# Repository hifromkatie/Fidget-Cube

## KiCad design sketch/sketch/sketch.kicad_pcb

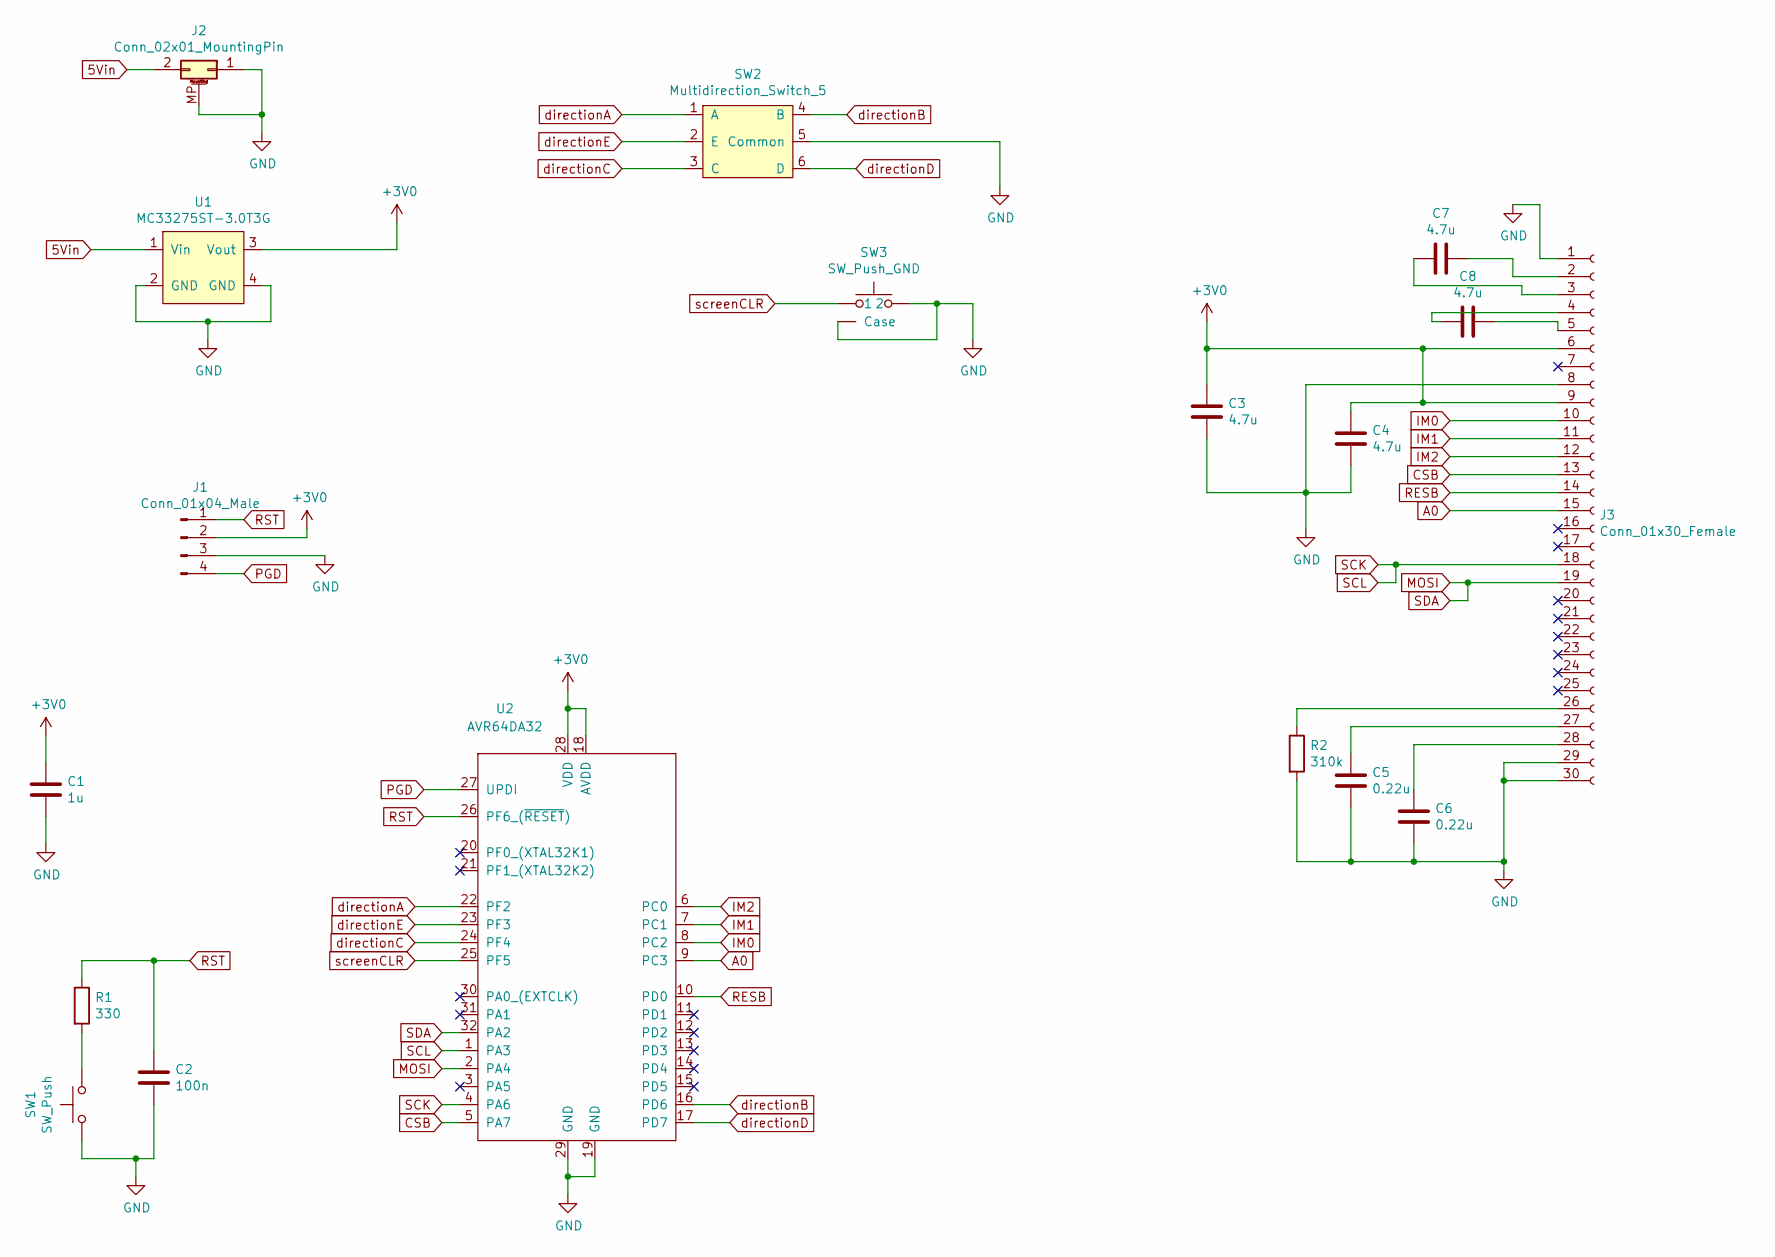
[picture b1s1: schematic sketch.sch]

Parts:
C1: 1u; C_0603_1608Metric_Pad1.08x0.95mm_HandSolder; Farnell Part Number 2409038
C2: 100n; C_0603_1608Metric_Pad1.08x0.95mm_HandSolder; Farnell Part Number 2320813
C3, C4, C7, C8: 4.7u; C_0603_1608Metric_Pad1.08x0.95mm_HandSolder; Farnell Part Number 9227784
C5, C6: 0.22u; C_0603_1608Metric_Pad1.08x0.95mm_HandSolder; Farnell Part Number 2627437
J1: Conn_01x04_Male; PinHeader_1x04_P2.54mm_Vertical
J2: Conn_02x01_MountingPin; Molex_PicoBlade_53398-0271_1x02-1MP_P1.25mm_Vertical; Farnell Part Number 1125366
J3: Conn_01x30_Female; screenConnector_30pin_0.7pitch
R1: 330; R_0603_1608Metric_Pad0.98x0.95mm_HandSolder; Farnell Part Number 2447339
R2: 310k; R_0603_1608Metric_Pad0.98x0.95mm_HandSolder; Farnell Part Number 2337128
SW1: SW_Push; WS-TASV; Farnell Part Number 1867991
SW2: Multidirection_Switch_5; MCMT5; Farnell Part Number 1316987
SW3: SW_Push_GND; MSLPT5252-BG; Farnell Part Number 2991002
U1: MC33275ST-3.0T3G; SOT-223; Farnell Part Number 2728244
U2: AVR64DA32; TQFP-32_7x7mm_P0.8mm; Farnell Part Number 3576891

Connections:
5Vin: J2.2, U1.1 (Vin)
+3V0: C1.1, C3.1, C4.1, J1.2, J3.6, J3.9, U1.3 (Vout), U2.18 (AVDD), U2.28 (VDD)
A0: J3.15, U2.9 (PC3)
CSB: J3.13, U2.5 (PA7)
GND: C1.2, C2.2, C3.2, C4.2, C5.2, C6.2, J1.3, J2.1, J2.MP (MountPin), J3.1, J3.8, J3.29, J3.30, R2.2, SW1.1, SW2.5 (Common), SW3.2, SW3.3 (Case), U1.2 (GND), U1.4 (GND), U2.19 (GND), U2.29 (GND)
IM0: J3.10, U2.8 (PC2)
IM1: J3.11, U2.7 (PC1)
IM2: J3.12, U2.6 (PC0)
MOSI: J3.19, U2.2 (PA4), U2.32 (PA2)
unnamed: C5.1, J3.27
unnamed: C6.1, J3.28
unnamed: C7.1, J3.2
unnamed: C7.2, J3.3
unnamed: C8.1, J3.5
unnamed: C8.2, J3.4
unnamed: J3.26, R2.1
unnamed: R1.2, SW1.2
PGD: J1.4, U2.27 (UPDI)
RESB: J3.14, U2.10 (PD0)
RST: C2.1, J1.1, R1.1, U2.26 (PF6_(~RESET~))
SCK: J3.18, U2.1 (PA3), U2.4 (PA6)
directionA: SW2.1 (A), U2.22 (PF2)
directionB: SW2.4 (B), U2.16 (PD6)
directionC: SW2.3 (C), U2.24 (PF4)
directionD: SW2.6 (D), U2.17 (PD7)
directionE: SW2.2 (E), U2.23 (PF3)
screenCLR: SW3.1, U2.25 (PF5)

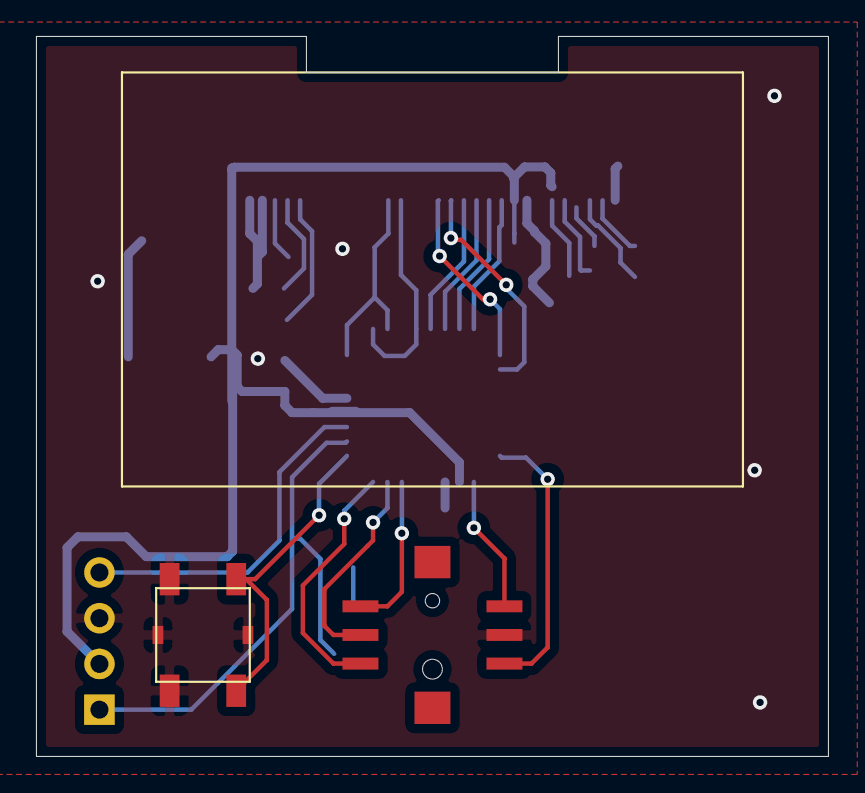
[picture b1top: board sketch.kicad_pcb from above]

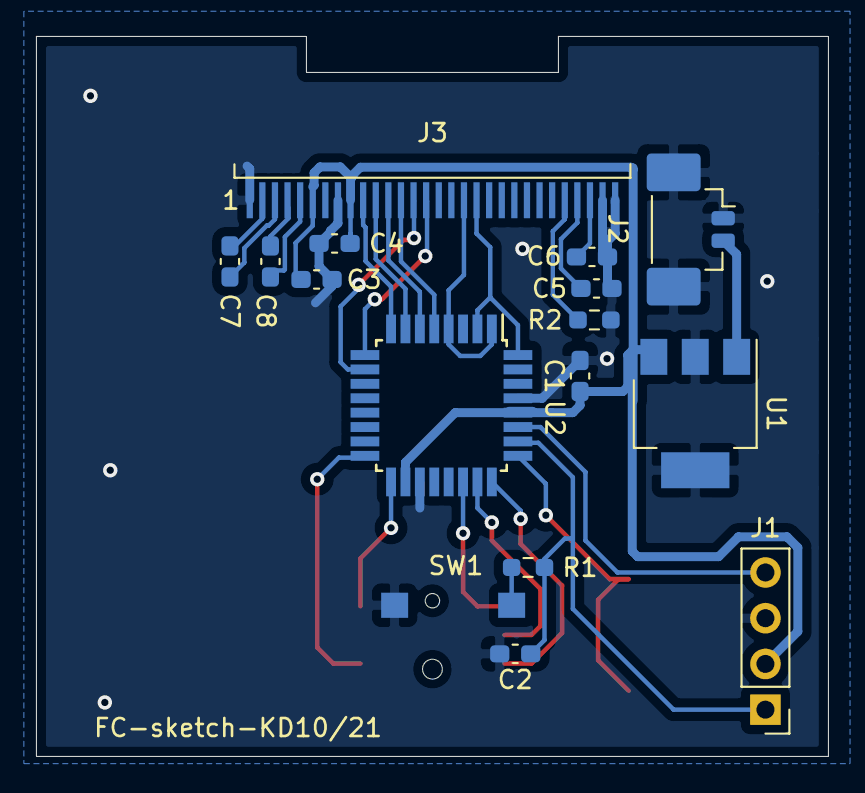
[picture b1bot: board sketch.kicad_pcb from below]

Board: 2 copper layers, 44.0 x 40.0 mm, 18 parts (16 on the bottom side), 27 nets.

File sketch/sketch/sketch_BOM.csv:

Source:,/home/katie/Projects/FidgetCube/circuit/sketch/sketch/sketch.sch,,,,,,
Date:,Tue 23 Nov 2021 22:22:43 GMT,,,,,,
Tool:,Eeschema 5.1.10-88a1d61d58~90~ubuntu20.04.1,,,,,,
Generator:,/usr/share/kicad/plugins/bom_csv_grouped_by_value.py,,,,,,
Component Count:,18,,,,,,
,,,,,,,
Individual Components:,,,,,,,
,,,,,,,
Item,Qty,Reference(s),Value,LibPart,Footprint,Datasheet,Farnell Part Number
,,C1,1u,Device:C,Capacitor_SMD:C_0603_1608Metric_Pad1.08x0.95mm_HandSolder,~,2409038
,,C2,100n,Device:C,Capacitor_SMD:C_0603_1608Metric_Pad1.08x0.95mm_HandSolder,~,2320813
,,C3,4.7u,Device:C,Capacitor_SMD:C_0603_1608Metric_Pad1.08x0.95mm_HandSolder,~,9227784
,,C4,4.7u,Device:C,Capacitor_SMD:C_0603_1608Metric_Pad1.08x0.95mm_HandSolder,~,9227784
,,C5,0.22u,Device:C,Capacitor_SMD:C_0603_1608Metric_Pad1.08x0.95mm_HandSolder,~,2627437
,,C6,0.22u,Device:C,Capacitor_SMD:C_0603_1608Metric_Pad1.08x0.95mm_HandSolder,~,2627437
,,C7,4.7u,Device:C,Capacitor_SMD:C_0603_1608Metric_Pad1.08x0.95mm_HandSolder,~,9227784
,,C8,4.7u,Device:C,Capacitor_SMD:C_0603_1608Metric_Pad1.08x0.95mm_HandSolder,~,9227784
,,J1,Conn_01x04_Male,Connector:Conn_01x04_Male,Connector_PinHeader_2.54mm:PinHeader_1x04_P2.54mm_Vertical,~,-
,,J2,Conn_02x01_MountingPin,Connector_Generic_MountingPin:Conn_02x01_MountingPin,Connector_Molex:Molex_PicoBlade_53398-0271_1x02-1MP_P1.25mm_Vertical,~,1125366
,,J3,Conn_01x30_Female,Connector:Conn_01x30_Female,My_Footprints:screenConnector_30pin_0.7pitch,~,-
,,R1,330,Device:R,Resistor_SMD:R_0603_1608Metric_Pad0.98x0.95mm_HandSolder,~,2447339
,,R2,310k,Device:R,Resistor_SMD:R_0603_1608Metric_Pad0.98x0.95mm_HandSolder,~,2337128
,,SW1,SW_Push,Switch:SW_Push,My_Footprints:WS-TASV,https://www.farnell.com/datasheets/1913847.pdf,1867991
,,SW2,Multidirection_Switch_5,My_Library:Multidirection_Switch_5,My_Footprints:MCMT5,https://www.farnell.com/datasheets/3169924.pdf,1316987
,,SW3,SW_Push_GND,My_Library:SW_Push_GND,My_Footprints:MSLPT5252-BG,https://uk.farnell.com/alcoswitch-te-connectivity/mslpt5252b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,2991002
,,U1,MC33275ST-3.0T3G,My_Library:MC33275ST-3.0T3G,Package_TO_SOT_SMD:SOT-223,https://www.farnell.com/datasheets/1904484.pdf,2728244
,,U2,AVR64DA32,My_Library:AVR64DA32,Package_QFP:TQFP-32_7x7mm_P0.8mm,https://www.farnell.com/datasheets/3165060.pdf,3576891
,,,,,,,
,,,,,,,
,,,,,,,
Collated Components:,,,,,,,
,,,,,,,
Item,Qty,Reference(s),Value,LibPart,Footprint,Datasheet,F
1,1,C1,1u,Device:C,Capacitor_SMD:C_0603_1608Metric_Pad1.08x0.95mm_HandSolder,~,2409038
2,1,C2,100n,Device:C,Capacitor_SMD:C_0603_1608Metric_Pad1.08x0.95mm_HandSolder,~,2320813
3,4,"C3, C4, C7, C8",4.7u,Device:C,Capacitor_SMD:C_0603_1608Metric_Pad1.08x0.95mm_HandSolder,~,9227784
4,2,"C5, C6",0.22u,Device:C,Capacitor_SMD:C_0603_1608Metric_Pad1.08x0.95mm_HandSolder,~,2627437
5,1,J1,Conn_01x04_Male,Connector:Conn_01x04_Male,Connector_PinHeader_2.54mm:PinHeader_1x04_P2.54mm_Vertical,~,-
6,1,J2,Conn_02x01_MountingPin,Connector_Generic_MountingPin:Conn_02x01_MountingPin,Connector_Molex:Molex_PicoBlade_53398-0271_1x02-1MP_P1.25mm_Vertical,~,1125366
7,1,J3,Conn_01x30_Female,Connector:Conn_01x30_Female,My_Footprints:screenConnector_30pin_0.7pitch,~,-
8,1,R1,330,Device:R,Resistor_SMD:R_0603_1608Metric_Pad0.98x0.95mm_HandSolder,~,2447339
9,1,R2,310k,Device:R,Resistor_SMD:R_0603_1608Metric_Pad0.98x0.95mm_HandSolder,~,2337128
10,1,SW1,SW_Push,Switch:SW_Push,My_Footprints:WS-TASV,https://www.farnell.com/datasheets/1913847.pdf,1867991
11,1,SW2,Multidirection_Switch_5,My_Library:Multidirection_Switch_5,My_Footprints:MCMT5,https://www.farnell.com/datasheets/3169924.pdf,1316987
12,1,SW3,SW_Push_GND,My_Library:SW_Push_GND,My_Footprints:MSLPT5252-BG,https://uk.farnell.com/alcoswitch-te-connectivity/mslpt5252b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,2991002
13,1,U1,MC33275ST-3.0T3G,My_Library:MC33275ST-3.0T3G,Package_TO_SOT_SMD:SOT-223,https://www.farnell.com/datasheets/1904484.pdf,2728244
14,1,U2,AVR64DA32,My_Library:AVR64DA32,Package_QFP:TQFP-32_7x7mm_P0.8mm,https://www.farnell.com/datasheets/3165060.pdf,3576891

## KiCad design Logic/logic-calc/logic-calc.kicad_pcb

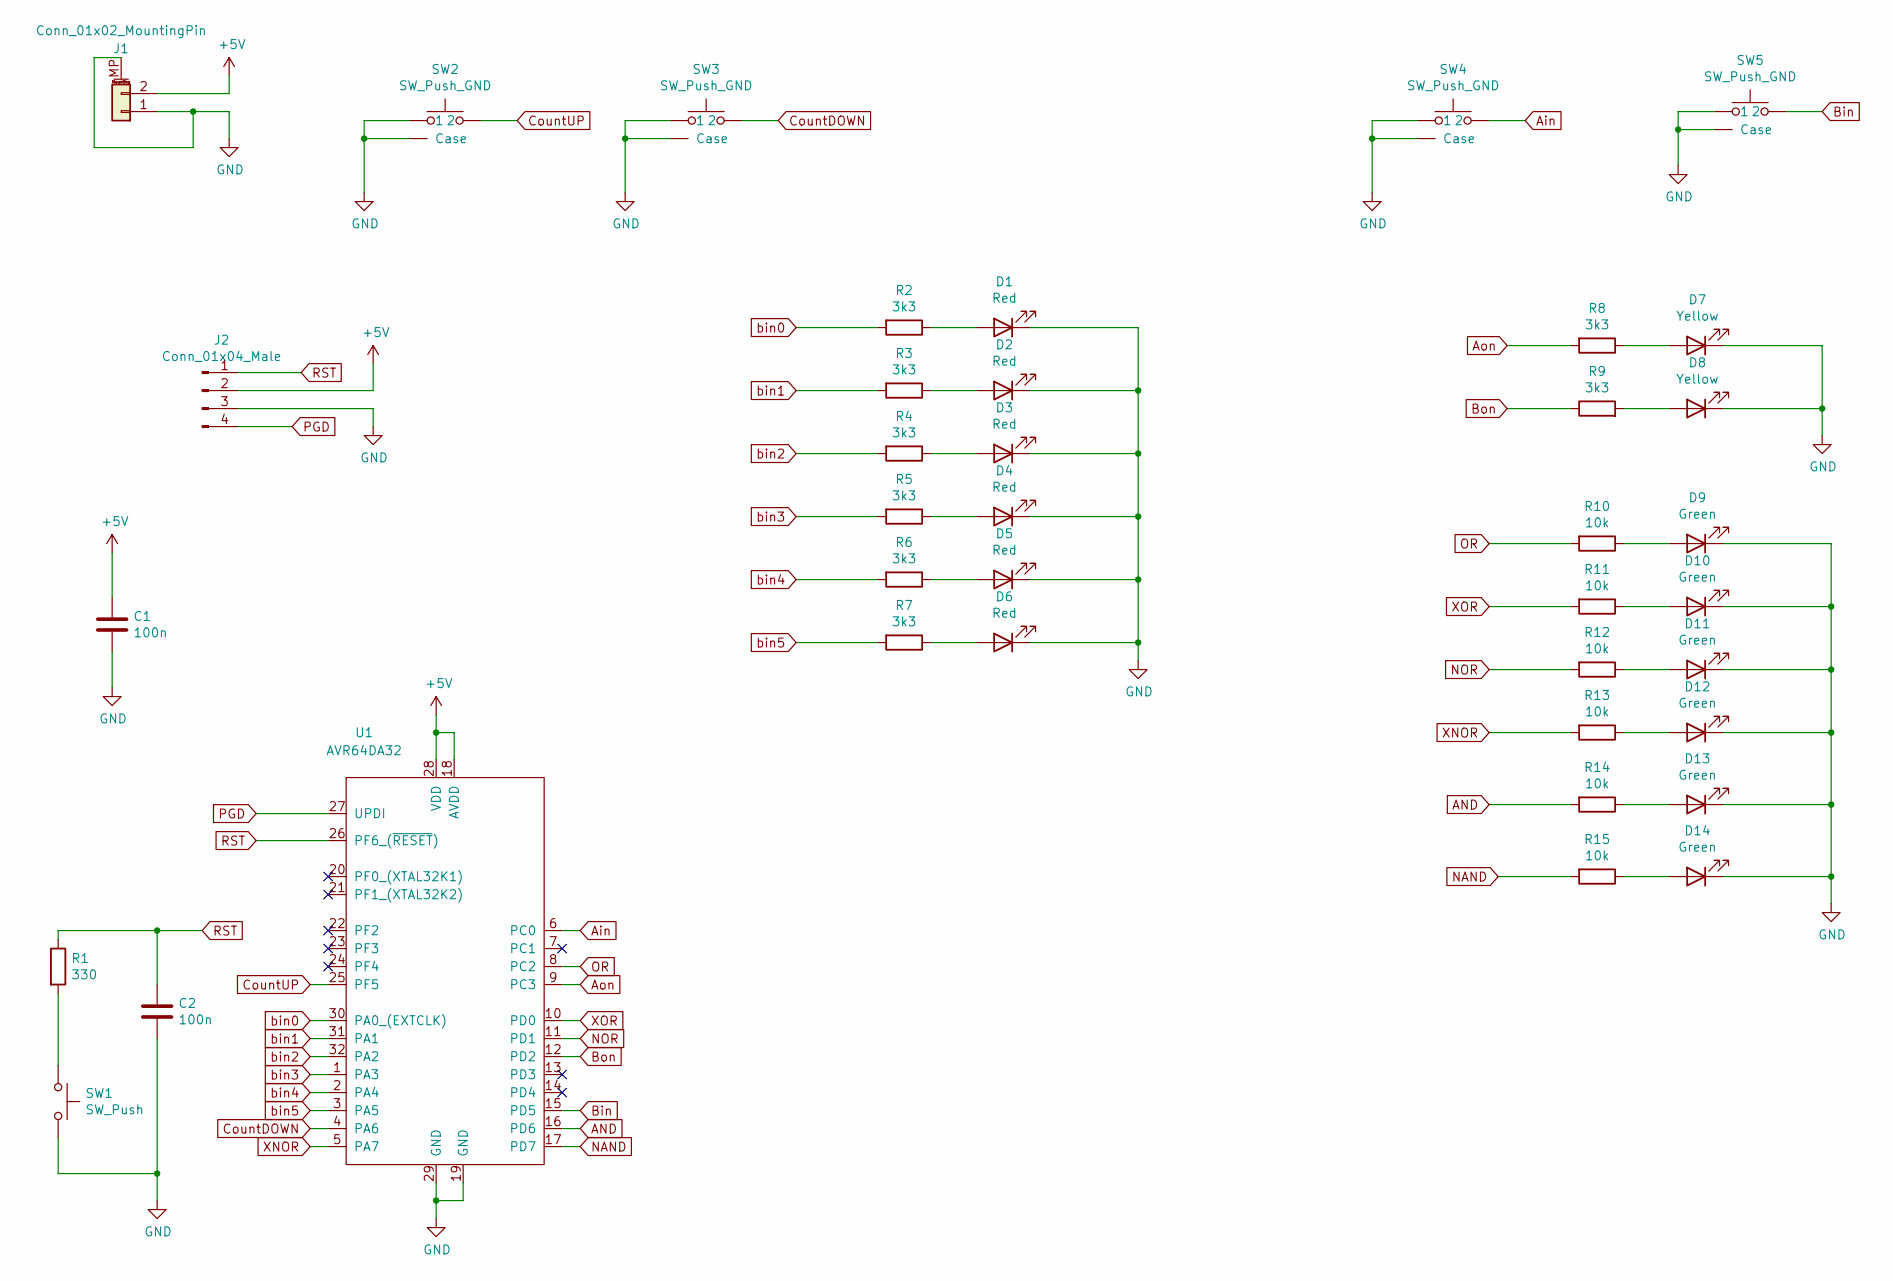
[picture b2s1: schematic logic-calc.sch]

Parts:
C1, C2: 100n; C_0603_1608Metric_Pad1.08x0.95mm_HandSolder
D1, D2, D3, D4, D5, D6: Red; LED_0805_2012Metric_Pad1.15x1.40mm_HandSolder
D7, D8: Yellow; LED_0805_2012Metric_Pad1.15x1.40mm_HandSolder
D9, D10, D11, D12, D13, D14: Green; LED_0805_2012Metric_Pad1.15x1.40mm_HandSolder
J1: Conn_01x02_MountingPin; Molex_PicoBlade_53398-0271_1x02-1MP_P1.25mm_Vertical
J2: Conn_01x04_Male; PinHeader_1x04_P2.54mm_Vertical
R1: 330; R_0603_1608Metric_Pad0.98x0.95mm_HandSolder
R2, R3, R4, R5, R6, R7, R8, R9: 3k3; R_0603_1608Metric_Pad0.98x0.95mm_HandSolder
R10, R11, R12, R13, R14, R15: 10k; R_0603_1608Metric_Pad0.98x0.95mm_HandSolder
SW1: SW_Push; WS-TASV
SW2, SW3, SW4, SW5: SW_Push_GND; MSLPT5252-BG
U1: AVR64DA32; TQFP-32_7x7mm_P0.8mm

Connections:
+5V: C1.1, J1.2, J2.2, U1.18 (AVDD), U1.28 (VDD)
AND: R14.2, U1.16 (PD6)
Ain: SW4.2, U1.6 (PC0)
Aon: R8.2, U1.9 (PC3)
Bin: SW5.2, U1.15 (PD5)
Bon: R9.1, U1.12 (PD2)
CountDOWN: SW3.2, U1.4 (PA6)
CountUP: SW2.2, U1.25 (PF5)
GND: C1.2, C2.2, D1.1 (K), D2.1 (K), D3.1 (K), D4.1 (K), D5.1 (K), D6.1 (K), D7.1 (K), D8.1 (K), D9.1 (K), D10.1 (K), D11.1 (K), D12.1 (K), D13.1 (K), D14.1 (K), J1.1, J1.MP (MountPin), J2.3, SW1.2, SW2.1, SW2.3 (Case), SW3.1, SW3.3 (Case), SW4.1, SW4.3 (Case), SW5.1, SW5.3 (Case), U1.19 (GND), U1.29 (GND)
NAND: R15.2, U1.17 (PD7)
NOR: R12.2, U1.11 (PD1)
unnamed: D1.2 (A), R2.1
unnamed: D2.2 (A), R3.1
unnamed: D3.2 (A), R4.1
unnamed: D4.2 (A), R5.1
unnamed: D5.2 (A), R6.1
unnamed: D6.2 (A), R7.1
unnamed: D7.2 (A), R8.1
unnamed: D8.2 (A), R9.2
unnamed: D9.2 (A), R10.1
unnamed: D10.2 (A), R11.1
unnamed: D11.2 (A), R12.1
unnamed: D12.2 (A), R13.1
unnamed: D13.2 (A), R14.1
unnamed: D14.2 (A), R15.1
unnamed: R1.2, SW1.1
OR: R10.2, U1.8 (PC2)
PGD: J2.4, U1.27 (UPDI)
RST: C2.1, J2.1, R1.1, U1.26 (PF6_(~RESET~))
XNOR: R13.2, U1.5 (PA7)
XOR: R11.2, U1.10 (PD0)
bin0: R2.2, U1.30 (PA0_(EXTCLK))
bin1: R3.2, U1.31 (PA1)
bin2: R4.2, U1.32 (PA2)
bin3: R5.2, U1.1 (PA3)
bin4: R6.2, U1.2 (PA4)
bin5: R7.2, U1.3 (PA5)

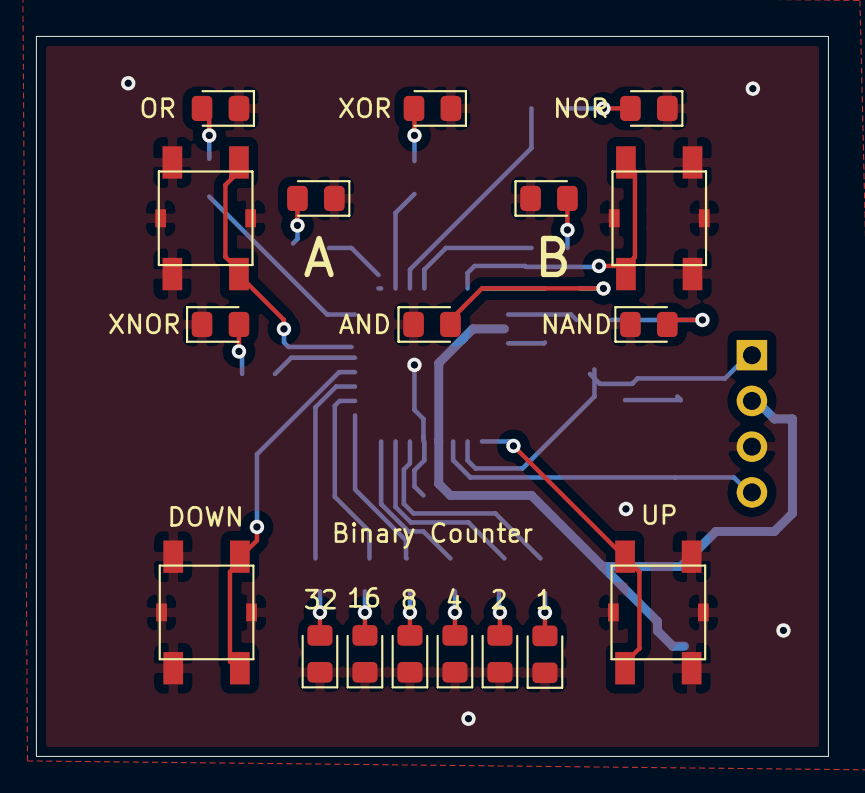
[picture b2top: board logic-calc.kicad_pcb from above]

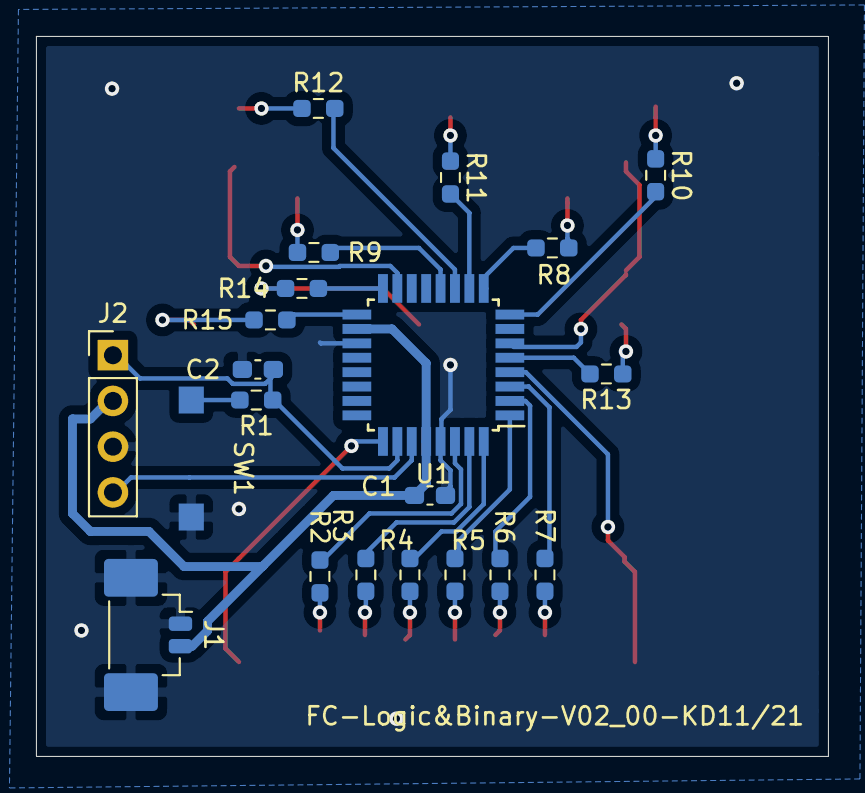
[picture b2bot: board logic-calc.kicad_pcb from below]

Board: 2 copper layers, 44.0 x 40.0 mm, 39 parts (21 on the bottom side), 37 nets.

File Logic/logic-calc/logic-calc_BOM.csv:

Source:,/home/katie/Projects/FidgetCube/circuit/Logic/logic-calc/logic-calc.sch,,,,,
Date:,Tue 23 Nov 2021 22:20:12 GMT,,,,,
Tool:,Eeschema 5.1.10-88a1d61d58~90~ubuntu20.04.1,,,,,
Generator:,/usr/share/kicad/plugins/bom_csv_grouped_by_value.py,,,,,
Component Count:,39,,,,,
,,,,,,
Individual Components:,,,,,,
,,,,,,
Item,Qty,Reference(s),Value,LibPart,Footprint,Farnell Order Code
,,C1,100n,Device:C,Capacitor_SMD:C_0603_1608Metric_Pad1.08x0.95mm_HandSolder,2320813
,,C2,100n,Device:C,Capacitor_SMD:C_0603_1608Metric_Pad1.08x0.95mm_HandSolder,2320813
,,D1,Red,Device:LED,LED_SMD:LED_0805_2012Metric_Pad1.15x1.40mm_HandSolder,3015159
,,D2,Red,Device:LED,LED_SMD:LED_0805_2012Metric_Pad1.15x1.40mm_HandSolder,3015159
,,D3,Red,Device:LED,LED_SMD:LED_0805_2012Metric_Pad1.15x1.40mm_HandSolder,3015159
,,D4,Red,Device:LED,LED_SMD:LED_0805_2012Metric_Pad1.15x1.40mm_HandSolder,3015159
,,D5,Red,Device:LED,LED_SMD:LED_0805_2012Metric_Pad1.15x1.40mm_HandSolder,3015159
,,D6,Red,Device:LED,LED_SMD:LED_0805_2012Metric_Pad1.15x1.40mm_HandSolder,3015159
,,D7,Yellow,Device:LED,LED_SMD:LED_0805_2012Metric_Pad1.15x1.40mm_HandSolder,1686073
,,D8,Yellow,Device:LED,LED_SMD:LED_0805_2012Metric_Pad1.15x1.40mm_HandSolder,1686073
,,D9,Green,Device:LED,LED_SMD:LED_0805_2012Metric_Pad1.15x1.40mm_HandSolder,3130210
,,D10,Green,Device:LED,LED_SMD:LED_0805_2012Metric_Pad1.15x1.40mm_HandSolder,3130210
,,D11,Green,Device:LED,LED_SMD:LED_0805_2012Metric_Pad1.15x1.40mm_HandSolder,3130210
,,D12,Green,Device:LED,LED_SMD:LED_0805_2012Metric_Pad1.15x1.40mm_HandSolder,3130210
,,D13,Green,Device:LED,LED_SMD:LED_0805_2012Metric_Pad1.15x1.40mm_HandSolder,3130210
,,D14,Green,Device:LED,LED_SMD:LED_0805_2012Metric_Pad1.15x1.40mm_HandSolder,3130210
,,J1,Conn_01x02_MountingPin,Connector_Generic_MountingPin:Conn_01x02_MountingPin,Connector_Molex:Molex_PicoBlade_53398-0271_1x02-1MP_P1.25mm_Vertical,	1125366
,,J2,Conn_01x04_Male,Connector:Conn_01x04_Male,Connector_PinHeader_2.54mm:PinHeader_1x04_P2.54mm_Vertical,NA
,,R1,330,Device:R,Resistor_SMD:R_0603_1608Metric_Pad0.98x0.95mm_HandSolder,2447339
,,R2,3k3,Device:R,Resistor_SMD:R_0603_1608Metric_Pad0.98x0.95mm_HandSolder,
,,R3,3k3,Device:R,Resistor_SMD:R_0603_1608Metric_Pad0.98x0.95mm_HandSolder,
,,R4,3k3,Device:R,Resistor_SMD:R_0603_1608Metric_Pad0.98x0.95mm_HandSolder,
,,R5,3k3,Device:R,Resistor_SMD:R_0603_1608Metric_Pad0.98x0.95mm_HandSolder,
,,R6,3k3,Device:R,Resistor_SMD:R_0603_1608Metric_Pad0.98x0.95mm_HandSolder,
,,R7,3k3,Device:R,Resistor_SMD:R_0603_1608Metric_Pad0.98x0.95mm_HandSolder,
,,R8,R,Device:R,Resistor_SMD:R_0603_1608Metric_Pad0.98x0.95mm_HandSolder,
,,R9,R,Device:R,Resistor_SMD:R_0603_1608Metric_Pad0.98x0.95mm_HandSolder,
,,R10,10k,Device:R,Resistor_SMD:R_0603_1608Metric_Pad0.98x0.95mm_HandSolder,
,,R11,10k,Device:R,Resistor_SMD:R_0603_1608Metric_Pad0.98x0.95mm_HandSolder,
,,R12,10k,Device:R,Resistor_SMD:R_0603_1608Metric_Pad0.98x0.95mm_HandSolder,
,,R13,10k,Device:R,Resistor_SMD:R_0603_1608Metric_Pad0.98x0.95mm_HandSolder,
,,R14,10k,Device:R,Resistor_SMD:R_0603_1608Metric_Pad0.98x0.95mm_HandSolder,
,,R15,10k,Device:R,Resistor_SMD:R_0603_1608Metric_Pad0.98x0.95mm_HandSolder,
,,SW1,SW_Push,Switch:SW_Push,My_Footprints:WS-TASV,	1867991
,,SW2,SW_Push_GND,My_Library:SW_Push_GND,My_Footprints:MSLPT5252-BG,	2991002
,,SW3,SW_Push_GND,My_Library:SW_Push_GND,My_Footprints:MSLPT5252-BG,	2991002
,,SW4,SW_Push_GND,My_Library:SW_Push_GND,My_Footprints:MSLPT5252-BG,	2991002
,,SW5,SW_Push_GND,My_Library:SW_Push_GND,My_Footprints:MSLPT5252-BG,	2991002
,,U1,AVR64DA32,My_Library:AVR64DA32,Package_QFP:TQFP-32_7x7mm_P0.8mm,	3576891
,,,,,,
,,,,,,
,,,,,,
Collated Components:,,,,,,
,,,,,,
Item,Qty,Reference(s),Value,LibPart,Footprint,F
1,2,"C1, C2",100n,Device:C,Capacitor_SMD:C_0603_1608Metric_Pad1.08x0.95mm_HandSolder,2320813
2,6,"D1, D2, D3, D4, D5, D6",Red,Device:LED,LED_SMD:LED_0805_2012Metric_Pad1.15x1.40mm_HandSolder,3015159
3,2,"D7, D8",Yellow,Device:LED,LED_SMD:LED_0805_2012Metric_Pad1.15x1.40mm_HandSolder,1686073
4,6,"D9, D10, D11, D12, D13, D14",Green,Device:LED,LED_SMD:LED_0805_2012Metric_Pad1.15x1.40mm_HandSolder,3130210
5,1,J1,Conn_01x02_MountingPin,Connector_Generic_MountingPin:Conn_01x02_MountingPin,Connector_Molex:Molex_PicoBlade_53398-0271_1x02-1MP_P1.25mm_Vertical,	1125366
6,1,J2,Conn_01x04_Male,Connector:Conn_01x04_Male,Connector_PinHeader_2.54mm:PinHeader_1x04_P2.54mm_Vertical,NA
7,1,R1,330,Device:R,Resistor_SMD:R_0603_1608Metric_Pad0.98x0.95mm_HandSolder,2447339
8,6,"R2, R3, R4, R5, R6, R7",3k3,Device:R,Resistor_SMD:R_0603_1608Metric_Pad0.98x0.95mm_HandSolder,
9,2,"R8, R9",R,Device:R,Resistor_SMD:R_0603_1608Metric_Pad0.98x0.95mm_HandSolder,
10,6,"R10, R11, R12, R13, R14, R15",10k,Device:R,Resistor_SMD:R_0603_1608Metric_Pad0.98x0.95mm_HandSolder,
11,1,SW1,SW_Push,Switch:SW_Push,My_Footprints:WS-TASV,	1867991
12,4,"SW2, SW3, SW4, SW5",SW_Push_GND,My_Library:SW_Push_GND,My_Footprints:MSLPT5252-BG,	2991002
13,1,U1,AVR64DA32,My_Library:AVR64DA32,Package_QFP:TQFP-32_7x7mm_P0.8mm,	3576891

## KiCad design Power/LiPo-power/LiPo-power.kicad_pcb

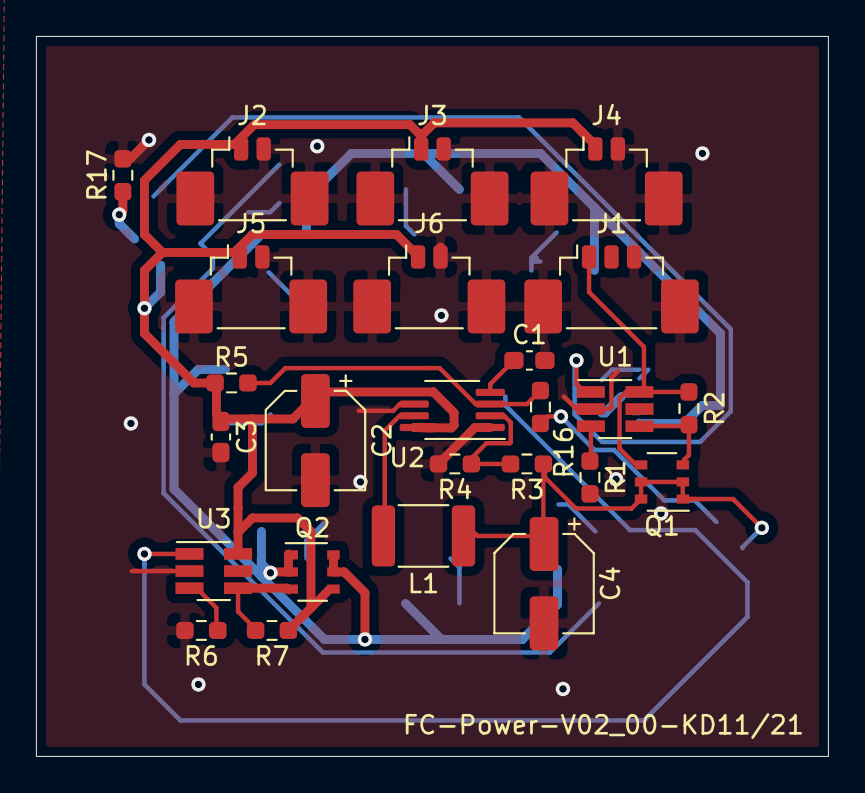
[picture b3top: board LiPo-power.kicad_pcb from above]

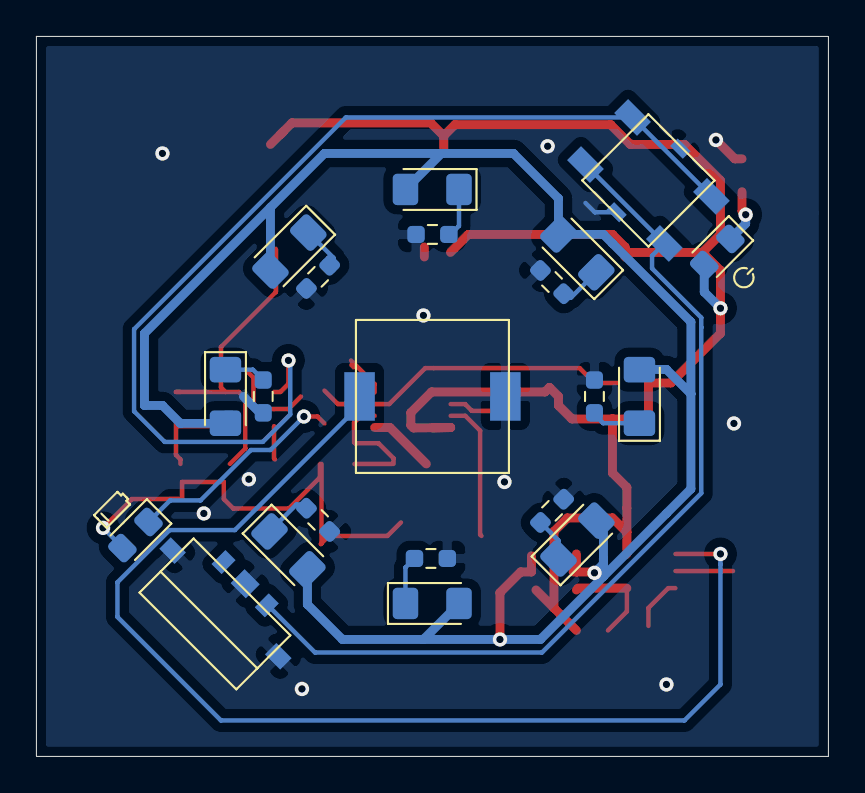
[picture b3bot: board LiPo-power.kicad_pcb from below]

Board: 2 copper layers, 44.0 x 40.0 mm, 46 parts (21 on the bottom side), 26 nets.

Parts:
C1, C3: 0.1u; C_0603_1608Metric_Pad1.08x0.95mm_HandSolder
C2, C4: 47u; CP_Elec_5x5.4
D1, D2, D3, D4, D5, D6, D7, D8: LED; LED_1206_3216Metric_Pad1.42x1.75mm_HandSolder
D9, D10: LED; LED_0805_2012Metric_Pad1.15x1.40mm_HandSolder
J1: Conn_01x03_Male; Molex_PicoBlade_53398-0371_1x03-1MP_P1.25mm_Vertical
J2, J3, J4, J5, J6: Conn_01x02_Female; Molex_PicoBlade_53398-0271_1x02-1MP_P1.25mm_Vertical
L1: 22u; L_1812_4532Metric_Pad1.30x3.40mm_HandSolder
Q1, Q2: PMN48XP; TSOP-6_1.65x3.05mm_P0.95mm
R1, R2, R6, R7: 10K; R_0603_1608Metric_Pad0.98x0.95mm_HandSolder
R3: 340K; R_0603_1608Metric_Pad0.98x0.95mm_HandSolder
R4: 260K; R_0603_1608Metric_Pad0.98x0.95mm_HandSolder
R5: 100k; R_0603_1608Metric_Pad0.98x0.95mm_HandSolder
R8, R9, R10, R11, R12, R13, R14, R15, R16, R17: R; R_0603_1608Metric_Pad0.98x0.95mm_HandSolder
SW1: SW_Push_GND; MSLPT5252-BG
SW2: SW_DPDT_x2+Case; JSX08001SAQNL
SW3: SW_Push; Switch-SKST
U1, U3: MAX16054; SOT-23-6_Handsoldering
U2: MAX1675; MSOP-8_3x3mm_P0.65mm

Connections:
+5V: C2.1, C3.1, D10.2, J2.1, J3.1, J4.1, J5.1, J6.1, Q2.4, R5.1, R7.1, U2.5, U2.8, U3.6
Battery_on: C4.1, D9.2, L1.1, Q1.1, Q1.2, Q1.5, Q1.6, R3.1
GND: C1.2, C2.2, C3.2, C4.2, J1.3, J1.MP, J2.2, J2.MP, J3.2, J3.MP, J4.2, J4.MP, J5.2, J5.MP, J6.2, J6.MP, R1.2, R4.2, R6.2, R8.1, R9.1, R10.1, R11.1, R12.1, R13.1, R14.1, R15.1, R17.2, SW1.3, SW2.2, SW2.4, SW3.1, U1.2, U2.1, U2.6, U3.2
LowBatt: R5.2, R16.2, U2.3
unnamed: C1.1, U2.4
unnamed: D1.1, R8.2
unnamed: D1.2, D2.2, D3.2, D4.2, D5.2, D6.2, D7.2, D8.2, Q2.1, Q2.2, Q2.5, Q2.6
unnamed: D2.1, R9.2
unnamed: D3.1, R10.2
unnamed: D4.1, R11.2
unnamed: D5.1, R12.2
unnamed: D6.1, R13.2
unnamed: D7.1, R14.2
unnamed: D8.1, R15.2
unnamed: D9.1, R16.1
unnamed: D10.1, R17.1
unnamed: J1.1, Q1.4, R2.1, U1.6
unnamed: L1.2, U2.7
unnamed: Q1.3, R2.2, U1.4
unnamed: Q2.3, R7.2, U3.4
unnamed: R1.1, U1.3
unnamed: R3.2, R4.1, U2.2
unnamed: R6.1, U3.3
unnamed: SW1.1, SW2.3
unnamed: SW1.2, U1.1
unnamed: SW3.2, U3.1

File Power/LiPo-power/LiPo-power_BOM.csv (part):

Source:,/home/katie/Projects/FidgetCube/circuit/Power/LiPo-power/LiPo-power.sch,,,,,,
Date:,Tue 23 Nov 2021 22:29:35 GMT,,,,,,
Tool:,Eeschema 5.1.10-88a1d61d58~90~ubuntu20.04.1,,,,,,
Generator:,/usr/share/kicad/plugins/bom_csv_grouped_by_value.py,,,,,,
Component Count:,46,,,,,,
,,,,,,,
Individual Components:,,,,,,,
,,,,,,,
Item,Qty,Reference(s),Value,LibPart,Footprint,Datasheet,Farnell Part Number
,,C1,0.1u,Device:C,Capacitor_SMD:C_0603_1608Metric_Pad1.08x0.95mm_HandSolder,~,2332586
,,C2,47u,Device:CP,Capacitor_SMD:CP_Elec_5x5.4,https://www.farnell.com/datasheets/3486024.pdf,2611420
,,C3,0.1u,Device:C,Capacitor_SMD:C_0603_1608Metric_Pad1.08x0.95mm_HandSolder,~,2332586
,,C4,47u,Device:CP,Capacitor_SMD:CP_Elec_5x5.4,https://www.farnell.com/datasheets/3486024.pdf,2611420
,,D1,Red,Device:LED,LED_SMD:LED_1206_3216Metric_Pad1.42x1.75mm_HandSolder,https://www.farnell.com/datasheets/3122976.pdf,3548447
,,D2,green,Device:LED,LED_SMD:LED_1206_3216Metric_Pad1.42x1.75mm_HandSolder,https://www.farnell.com/datasheets/3122976.pdf,3548452
,,D3,orange,Device:LED,LED_SMD:LED_1206_3216Metric_Pad1.42x1.75mm_HandSolder,https://www.farnell.com/datasheets/3122976.pdf,3548449
,,D4,blue,Device:LED,LED_SMD:LED_1206_3216Metric_Pad1.42x1.75mm_HandSolder,https://www.farnell.com/datasheets/3122976.pdf,3548453
,,D5,Red,Device:LED,LED_SMD:LED_1206_3216Metric_Pad1.42x1.75mm_HandSolder,https://www.farnell.com/datasheets/3122976.pdf,3548447
,,D6,green,Device:LED,LED_SMD:LED_1206_3216Metric_Pad1.42x1.75mm_HandSolder,https://www.farnell.com/datasheets/3122976.pdf,3548452
,,D7,orange,Device:LED,LED_SMD:LED_1206_3216Metric_Pad1.42x1.75mm_HandSolder,https://www.farnell.com/datasheets/3122976.pdf,3548449
,,D8,blue,Device:LED,LED_SMD:LED_1206_3216Metric_Pad1.42x1.75mm_HandSolder,https://www.farnell.com/datasheets/3122976.pdf,3548453
,,D9,red,Device:LED,LED_SMD:LED_0805_2012Metric_Pad1.15x1.40mm_HandSolder,~,3015159
,,D10,green,Device:LED,LED_SMD:LED_0805_2012Metric_Pad1.15x1.40mm_HandSolder,~,3130210
,,J1,Conn_01x03_Male,Connector:Conn_01x03_Male,Connector_Molex:Molex_PicoBlade_53398-0371_1x03-1MP_P1.25mm_Vertical,~,1125353
,,J2,Conn_01x02_Female,Connector:Conn_01x02_Female,Connector_Molex:Molex_PicoBlade_53398-0271_1x02-1MP_P1.25mm_Vertical,~,1125366
,,J3,Conn_01x02_Female,Connector:Conn_01x02_Female,Connector_Molex:Molex_PicoBlade_53398-0271_1x02-1MP_P1.25mm_Vertical,~,1125366
,,J4,Conn_01x02_Female,Connector:Conn_01x02_Female,Connector_Molex:Molex_PicoBlade_53398-0271_1x02-1MP_P1.25mm_Vertical,~,1125366
,,J5,Conn_01x02_Female,Connector:Conn_01x02_Female,Connector_Molex:Molex_PicoBlade_53398-0271_1x02-1MP_P1.25mm_Vertical,~,1125366
,,J6,Conn_01x02_Female,Connector:Conn_01x02_Female,Connector_Molex:Molex_PicoBlade_53398-0271_1x02-1MP_P1.25mm_Vertical,~,1125366
,,L1,22u,Device:L,Inductor_SMD:L_1812_4532Metric_Pad1.30x3.40mm_HandSolder,https://www.farnell.com/datasheets/2851560.pdf,3227861
,,Q1,PMN48XP,Transistor_FET:PMN48XP,Package_SO:TSOP-6_1.65x3.05mm_P0.95mm,https://assets.nexperia.com/documents/data-sheet/PMN48XP.pdf,3438538
,,Q2,PMN48XP,Transistor_FET:PMN48XP,Package_SO:TSOP-6_1.65x3.05mm_P0.95mm,https://assets.nexperia.com/documents/data-sheet/PMN48XP.pdf,3438538
,,R1,10K,Device:R,Resistor_SMD:R_0603_1608Metric_Pad0.98x0.95mm_HandSolder,~,2332016
,,R2,10K,Device:R,Resistor_SMD:R_0603_1608Metric_Pad0.98x0.95mm_HandSolder,~,2332016
,,R3,340K,Device:R,Resistor_SMD:R_0603_1608Metric_Pad0.98x0.95mm_HandSolder,~,2138549
,,R4,260K,Device:R,Resistor_SMD:R_0603_1608Metric_Pad0.98x0.95mm_HandSolder,~,2447312
,,R5,100k,Device:R,Resistor_SMD:R_0603_1608Metric_Pad0.98x0.95mm_HandSolder,~,2447226
,,R6,10K,Device:R,Resistor_SMD:R_0603_1608Metric_Pad0.98x0.95mm_HandSolder,~,2332016
,,R7,10K,Device:R,Resistor_SMD:R_0603_1608Metric_Pad0.98x0.95mm_HandSolder,~,2332016
,,R8,3k3,Device:R,Resistor_SMD:R_0603_1608Metric_Pad0.98x0.95mm_HandSolder,~,2447359
,,R9,10k,Device:R,Resistor_SMD:R_0603_1608Metric_Pad0.98x0.95mm_HandSolder,~,2332016
,,R10,3k3,Device:R,Resistor_SMD:R_0603_1608Metric_Pad0.98x0.95mm_HandSolder,~,2447359
,,R11,10k,Device:R,Resistor_SMD:R_0603_1608Metric_Pad0.98x0.95mm_HandSolder,~,2332016
,,R12,3k3,Device:R,Resistor_SMD:R_0603_1608Metric_Pad0.98x0.95mm_HandSolder,~,2447359
,,R13,10k,Device:R,Resistor_SMD:R_0603_1608Metric_Pad0.98x0.95mm_HandSolder,~,2332016
,,R14,3k3,Device:R,Resistor_SMD:R_0603_1608Metric_Pad0.98x0.95mm_HandSolder,~,2447359
,,R15,10k,Device:R,Resistor_SMD:R_0603_1608Metric_Pad0.98x0.95mm_HandSolder,~,2332016
,,R16,3k3,Device:R,Resistor_SMD:R_0603_1608Metric_Pad0.98x0.95mm_HandSolder,~,2447359
,,R17,10k,Device:R,Resistor_SMD:R_0603_1608Metric_Pad0.98x0.95mm_HandSolder,~,2332016
,,SW1,SW_Push_GND,My_Library:SW_Push_GND,My_Footprints:MSLPT5252-BG,https://www.farnell.com/datasheets/2700094.pdf,2991002
,,SW2,SW_DPDT_x2+Case,My_Library:SW_DPDT_x2+Case,My_Footprints:JSX08001SAQNL,https://www.ckswitches.com/media/1419/jsx.pdf,2435152
,,SW3,SW_Push,Switch:SW_Push,My_Footprints:Switch-SKST,https://www.farnell.com/datasheets/2864506.pdf,3261838
,,U1,MAX16054,My_Library:MAX16054,Package_TO_SOT_SMD:SOT-23-6_Handsoldering,https://www.farnell.com/datasheets/2001897.pdf,2515822
,,U2,MAX1675,My_Library:MAX1675,Package_SO:MSOP-8_3x3mm_P0.65mm,https://www.farnell.com/datasheets/1904456.pdf,2514146
,,U3,MAX16054,My_Library:MAX16054,Package_TO_SOT_SMD:SOT-23-6_Handsoldering,https://www.farnell.com/datasheets/2001897.pdf,2515822
,,,,,,,
,,,,,,,
,,,,,,,
Collated Components:,,,,,,,
,,,,,,,
Item,Qty,Reference(s),Value,LibPart,Footprint,Datasheet,F
1,2,"C1, C3",0.1u,Device:C,Capacitor_SMD:C_0603_1608Metric_Pad1.08x0.95mm_HandSolder,~,2332586
2,2,"C2, C4",47u,Device:CP,Capacitor_SMD:CP_Elec_5x5.4,https://www.farnell.com/datasheets/3486024.pdf,2611420
3,2,"D1, D5",Red,Device:LED,LED_SMD:LED_1206_3216Metric_Pad1.42x1.75mm_HandSolder,https://www.farnell.com/datasheets/3122976.pdf,3548447
4,2,"D2, D6",green,Device:LED,LED_SMD:LED_1206_3216Metric_Pad1.42x1.75mm_HandSolder,https://www.farnell.com/datasheets/3122976.pdf,3548452
5,2,"D3, D7",orange,Device:LED,LED_SMD:LED_1206_3216Metric_Pad1.42x1.75mm_HandSolder,https://www.farnell.com/datasheets/3122976.pdf,3548449
6,2,"D4, D8",blue,Device:LED,LED_SMD:LED_1206_3216Metric_Pad1.42x1.75mm_HandSolder,https://www.farnell.com/datasheets/3122976.pdf,3548453
7,1,D9,red,Device:LED,LED_SMD:LED_0805_2012Metric_Pad1.15x1.40mm_HandSolder,~,3015159
8,1,D10,green,Device:LED,LED_SMD:LED_0805_2012Metric_Pad1.15x1.40mm_HandSolder,~,3130210
9,1,J1,Conn_01x03_Male,Connector:Conn_01x03_Male,Connector_Molex:Molex_PicoBlade_53398-0371_1x03-1MP_P1.25mm_Vertical,~,1125353
10,5,"J2, J3, J4, J5, J6",Conn_01x02_Female,Connector:Conn_01x02_Female,Connector_Molex:Molex_PicoBlade_53398-0271_1x02-1MP_P1.25mm_Vertical,~,1125366
11,1,L1,22u,Device:L,Inductor_SMD:L_1812_4532Metric_Pad1.30x3.40mm_HandSolder,https://www.farnell.com/datasheets/2851560.pdf,3227861
12,2,"Q1, Q2",PMN48XP,Transistor_FET:PMN48XP,Package_SO:TSOP-6_1.65x3.05mm_P0.95mm,https://assets.nexperia.com/documents/data-sheet/PMN48XP.pdf,3438538
13,4,"R1, R2, R6, R7",10K,Device:R,Resistor_SMD:R_0603_1608Metric_Pad0.98x0.95mm_HandSolder,~,2332016
14,1,R3,340K,Device:R,Resistor_SMD:R_0603_1608Metric_Pad0.98x0.95mm_HandSolder,~,2138549
15,1,R4,260K,Device:R,Resistor_SMD:R_0603_1608Metric_Pad0.98x0.95mm_HandSolder,~,2447312
16,1,R5,100k,Device:R,Resistor_SMD:R_0603_1608Metric_Pad0.98x0.95mm_HandSolder,~,2447226
17,5,"R8, R10, R12, R14, R16",3k3,Device:R,Resistor_SMD:R_0603_1608Metric_Pad0.98x0.95mm_HandSolder,~,2447359
18,5,"R9, R11, R13, R15, R17",10k,Device:R,Resistor_SMD:R_0603_1608Metric_Pad0.98x0.95mm_HandSolder,~,2332016
19,1,SW1,SW_Push_GND,My_Library:SW_Push_GND,My_Footprints:MSLPT5252-BG,https://www.farnell.com/datasheets/2700094.pdf,2991002
20,1,SW2,SW_DPDT_x2+Case,My_Library:SW_DPDT_x2+Case,My_Footprints:JSX08001SAQNL,https://www.ckswitches.com/media/1419/jsx.pdf,2435152
21,1,SW3,SW_Push,Switch:SW_Push,My_Footprints:Switch-SKST,https://www.farnell.com/datasheets/2864506.pdf,3261838
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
